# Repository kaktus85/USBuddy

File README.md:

# USBuddy
This repository contains all the available documentation and source files for USBuddy USB development tool project.
- A copy of this is also available on Google Drive: https://drive.google.com/drive/folders/0B7G3xJXZNLUpYzR0Vlo4bV9fNGM
- An article about this project is here: http://kaktuscircuits.blogspot.cz/2016/03/usbuddy.html and on Hackaday.io: https://hackaday.io/project/10372-usbuddy
- USBuddy can be purchased through Tindie: https://www.tindie.com/products/Kaktus/usbuddy-usb-development-tool/

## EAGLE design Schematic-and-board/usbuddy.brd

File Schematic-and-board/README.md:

# Schematic and Board
- Cadsoft Eagle source files for the PCB of USBuddy.
- A PNG schematic also included for a quick reference without having to install Eagle.
- Pinout of USBuddy header for quick reference in PNG file.

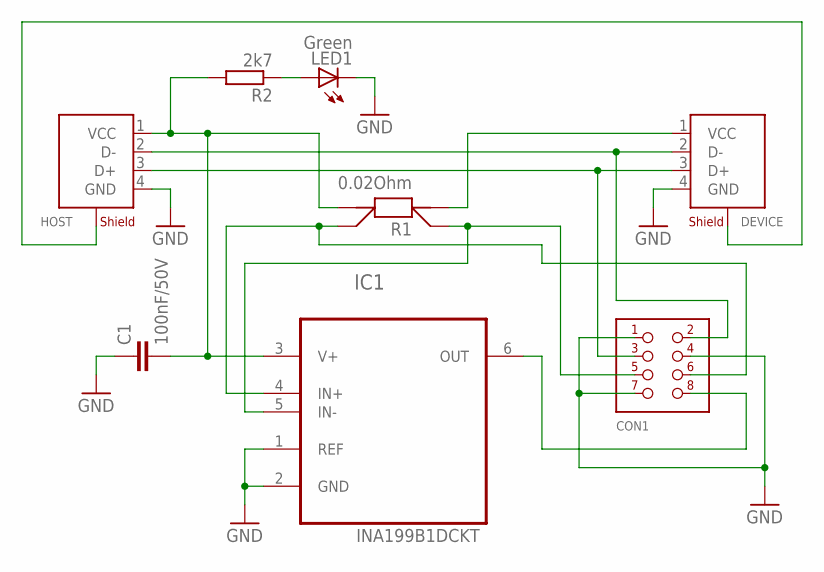
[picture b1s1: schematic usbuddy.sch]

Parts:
C1: 100nF/50V; C0603K
CON1: PINHEAD-02X04-SMT-2.54; 2X04-SMT-PINHEAD
DEVICE: USB-A-SMT; USB-A-SMT-UBA-4R-S14HD-4S
HOST: USB-B-SMT
IC1: INA199A2DCKR; SOT65P210X110-6N; MPN INA199B1DCKT
LED1: Green; CHIP-LED0603
R1: 0.02Ohm; 1206-4WIRE
R2: 2k7; R1206

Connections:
D+: CON1.3, DEVICE.3 (D+), HOST.3 (D+)
D-: CON1.2, DEVICE.2 (D-), HOST.2 (D-)
GND: C1.1, CON1.1, CON1.4, CON1.7, DEVICE.4 (GND), HOST.4 (GND), IC1.1 (REF), IC1.2 (GND), LED1.C
unnamed: CON1.5, IC1.5 (IN-), R1.V1
unnamed: CON1.8, IC1.6 (OUT)
unnamed: DEVICE.1 (VCC), R1.I1
unnamed: CON1.6, IC1.4 (IN+), R1.V2
unnamed: LED1.A, R2.1
SHIELD: DEVICE.S1 (SHIELD), DEVICE.S2 (SHIELD), DEVICE.S3 (SHIELD), DEVICE.S4 (SHIELD), HOST.S1 (SHIELD), HOST.S2 (SHIELD)
VBUS: C1.2, HOST.1 (VCC), IC1.3 (V+), R1.I2, R2.2

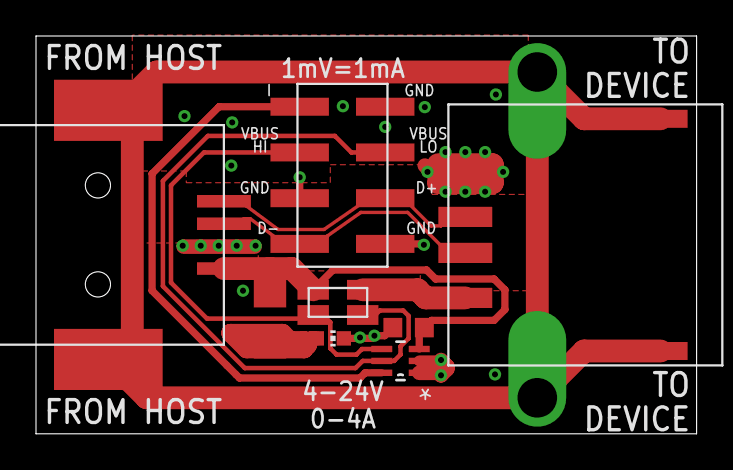
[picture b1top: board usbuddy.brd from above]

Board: 2 copper layers, 36.7 x 22.1 mm, 8 parts (0 on the bottom side), 10 nets.

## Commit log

2016-07-01 :tada: Added .gitattributes & .gitignore files
2016-07-01 Initial files
